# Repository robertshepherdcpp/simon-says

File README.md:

# simon-says
my fourth project for fallout

**what is this project**
- test out your memory with this memory game!
- this project tests your sequence memory, in having a sequence that increases in length after everytime you get it right
- see how far you can go! how many can you remember in a row

**assembly instructions**
- print out the pcb and the case, and purchase the components meantioned in the bom
- put the pcb in the case
- put on the lid. then attach the screws mentioned in the BOM to fix the pcb in place.
- flash the firmware to the xiao-esp32 through the arduino ide (via usb)
- keep it plugged into your computer, as that will be the power source!
- try and see how many you can remember!

**inspiration for the project**
- having played the sequence memory game on [human benchark](humanbenchmark.com), i wanted to have a physical version of this that i could play with!
- i thought it would be a good way to try and improve my memory as having it in physical form i think makes me more likely to use it.

**how it works**
- the project will show the seqence of keys 1 by 1, you simply copy these!
- see how many of these you can remember!
- if you have a high score, the project  will flash 3 times (this high score is stored on the permanent storage of esp-32 board. (using preferences.h)
- if you press the wrong key, then all leds will flash once, and the sequence will reset, (back to a seqeunce of length 1, then you have to memorize a new sequence)
- keep trying to beat the PB!

**how this project was made**
- case made using fusion360
- pcb made using kicad
- in the 3d model, the keycaps and cherry-switches were imported as step files from repos on github.

**screenshots**
the schematic:

the footprint:

pcb 3d:

the 3d model:

zine:

bom:

total project cost: $28.53 (however will already have components spare from other projects like cherry mx switches, key caps)

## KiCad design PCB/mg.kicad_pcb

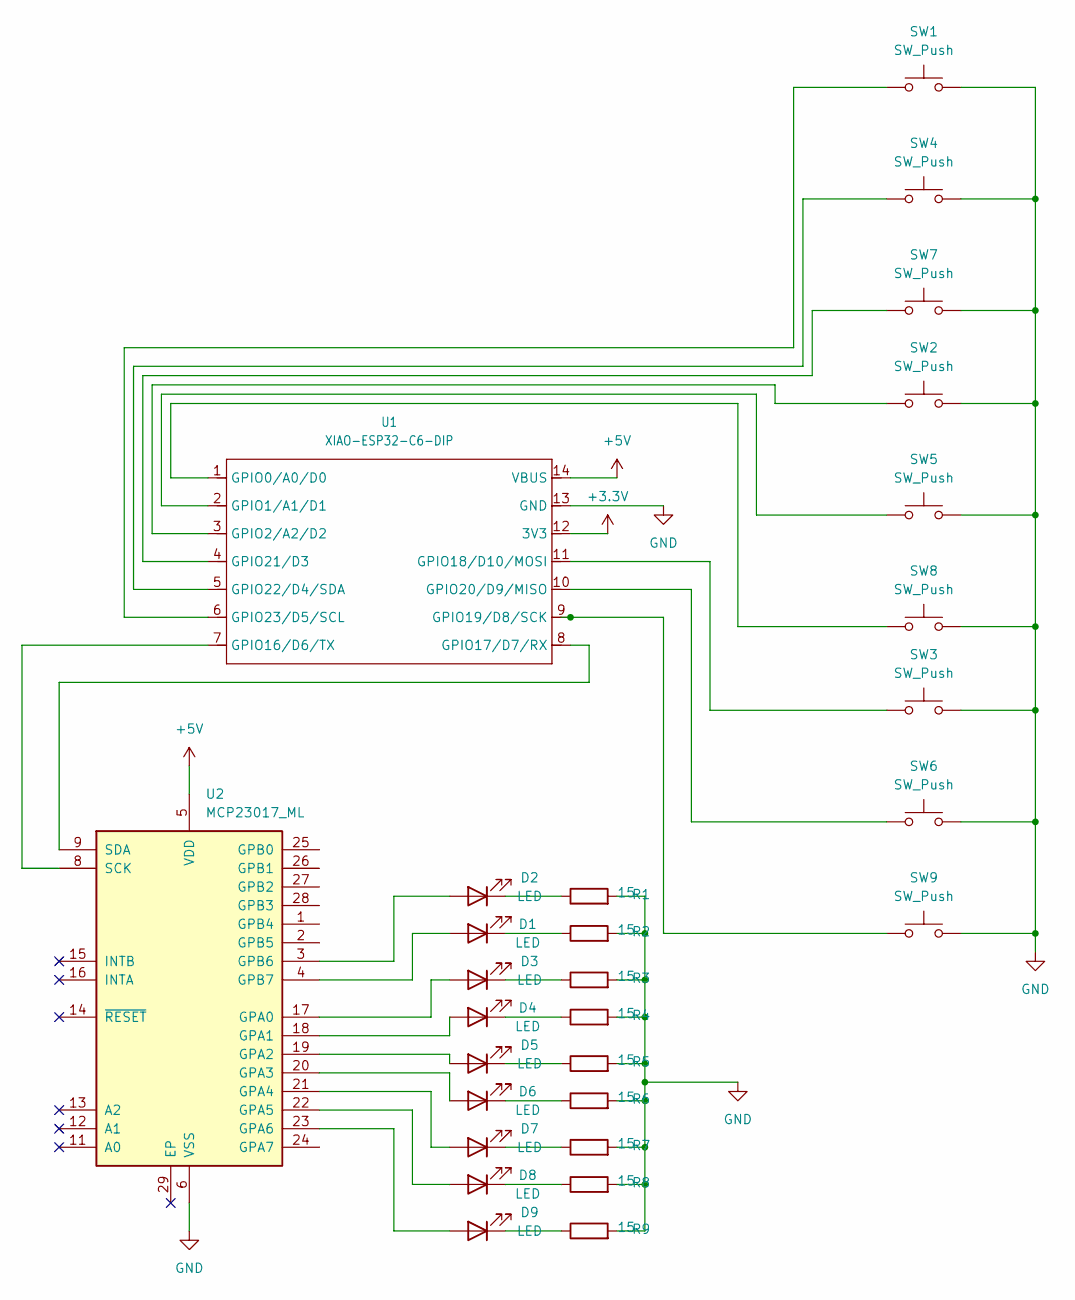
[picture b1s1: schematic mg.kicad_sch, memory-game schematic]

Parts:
D1, D2, D3, D4, D5, D6, D7, D8, D9: LED; LED_0603_1608Metric
R1, R2, R3, R4, R5, R6, R7, R8, R9: 15; R_0603_1608Metric
SW1, SW2, SW3, SW4, SW5, SW6, SW7, SW8, SW9: SW_Push; SW_Cherry_MX_1.00u_PCB
U1: XIAO-ESP32-C6-DIP
U2: MCP23017_ML; QFN-28-1EP_6x6mm_P0.65mm_EP4.25x4.25mm

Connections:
+3.3V: U1.12 (3V3)
+5V: U1.14 (VBUS), U2.5 (VDD)
GND: R1.2, R2.2, R3.2, R4.2, R5.2, R6.2, R7.2, R8.2, R9.2, SW1.2, SW2.2, SW3.2, SW4.2, SW5.2, SW6.2, SW7.2, SW8.2, SW9.2, U1.13 (GND), U2.6 (VSS)
unnamed: D1.2 (A), U2.4 (GPB7)
unnamed: D1.1 (K), R2.1
unnamed: D2.2 (A), U2.3 (GPB6)
unnamed: D2.1 (K), R1.1
unnamed: D3.2 (A), U2.17 (GPA0)
unnamed: D3.1 (K), R3.1
unnamed: D4.2 (A), U2.18 (GPA1)
unnamed: D4.1 (K), R4.1
unnamed: D5.2 (A), U2.19 (GPA2)
unnamed: D5.1 (K), R5.1
unnamed: D6.2 (A), U2.20 (GPA3)
unnamed: D6.1 (K), R6.1
unnamed: D7.2 (A), U2.21 (GPA4)
unnamed: D7.1 (K), R7.1
unnamed: D8.2 (A), U2.22 (GPA5)
unnamed: D8.1 (K), R8.1
unnamed: D9.2 (A), U2.23 (GPA6)
unnamed: D9.1 (K), R9.1
unnamed: SW8.1, U1.1 (GPIO0/A0/D0)
unnamed: SW5.1, U1.2 (GPIO1/A1/D1)
unnamed: SW2.1, U1.3 (GPIO2/A2/D2)
unnamed: U1.7 (GPIO16/D6/TX), U2.8 (SCK)
unnamed: U1.8 (GPIO17/D7/RX), U2.9 (SDA)
unnamed: SW3.1, U1.11 (GPIO18/D10/MOSI)
unnamed: SW9.1, U1.9 (GPIO19/D8/SCK)
unnamed: SW6.1, U1.10 (GPIO20/D9/MISO)
unnamed: SW7.1, U1.4 (GPIO21/D3)
unnamed: SW4.1, U1.5 (GPIO22/D4/SDA)
unnamed: SW1.1, U1.6 (GPIO23/D5/SCL)

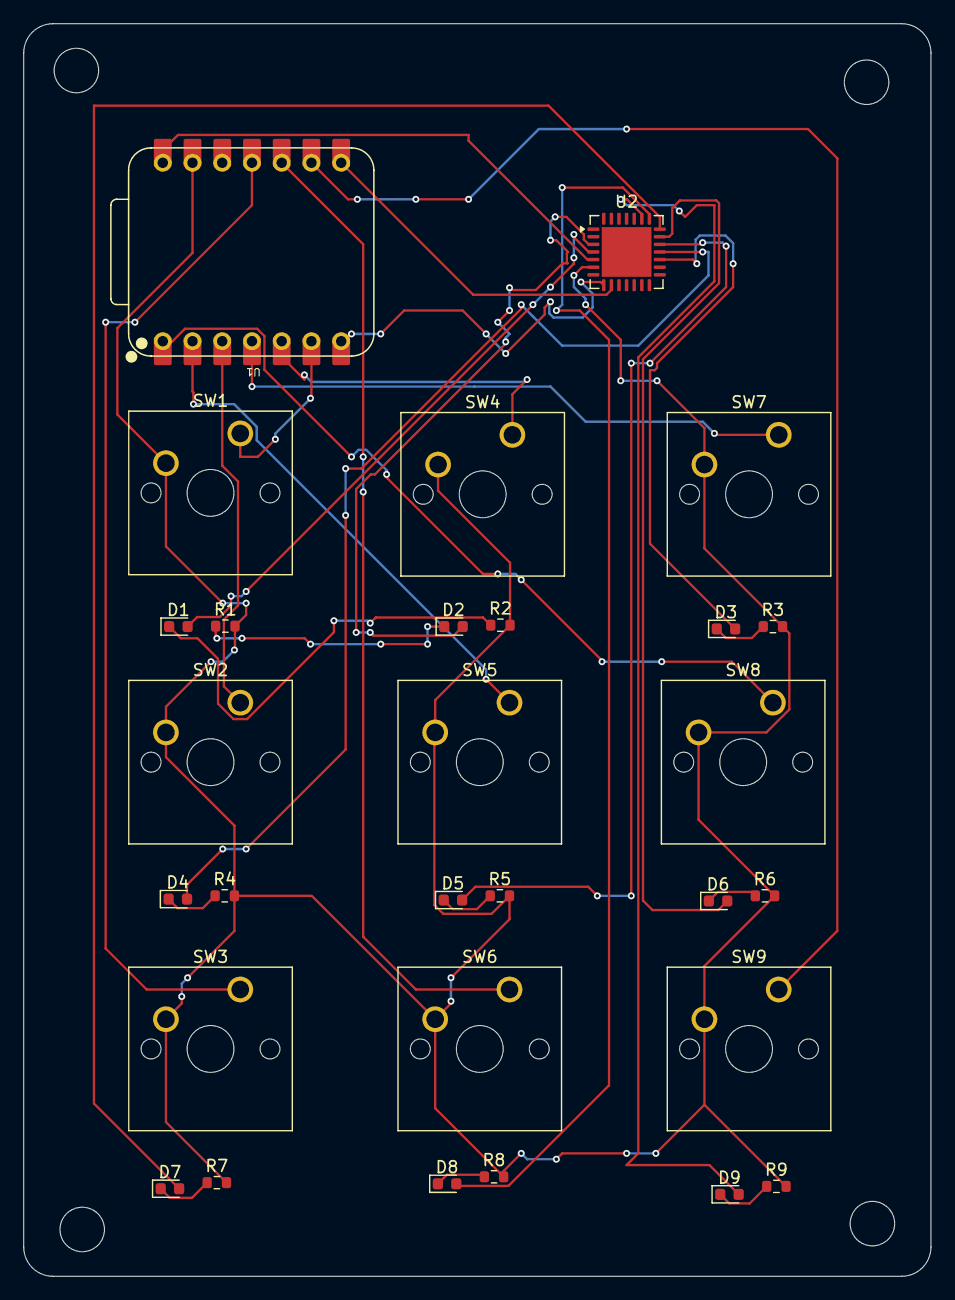
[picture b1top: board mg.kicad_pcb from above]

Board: 2 copper layers, 77.5 x 107.0 mm, 29 parts (0 on the bottom side), 31 nets.

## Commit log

2026-04-29 Enhance README with project information and instructions
    Expanded the README to include project details, usage instructions, inspiration, and how it works.
2026-04-29 add the pcb files
2026-04-29 Rename switch.step to CAD/switch.step
2026-04-29 Rename roductivv.f3d to CAD/roductivv.f3d
2026-04-29 Rename Cherry MX keycaps.step to CAD/Cherry MX keycaps.step
2026-04-29 Rename sketch_apr26a_copy_20260429135617.ino to firmware/sketch_apr26a_copy_20260429135617.ino
2026-04-29 Add new image to README.md zine section
2026-04-29 Rename Untitled (1).png to Zine/zine.png
2026-04-29 Update total project cost from $26.73 to $36.28
    Updated total project cost in the README.
2026-04-29 Fix formatting issue in BOM CSV for MCP23017
2026-04-29 Add BOM image and project cost information
    Added an image for the BOM section and provided cost details.
2026-05-01 Update README with additional information on usage
    Added a note about the 'how it works' section for more information.
2026-06-04 add the actual mcp23017 chip
2026-06-04 add new zine
2026-06-04 Rename Untitled (13).pdf to zine.pdf
2026-06-04 Update README with additional zine image
    Added a new image to the zine section of the README.
2026-06-04 add the updataed cherry mx keycaps step file
2026-06-09 Add total cost row to BOM CSV
2026-06-09 uploading the new pcb files (with the cutout in the pcb)
2026-06-09 Update images in README.md
    Removed and replaced images in the README.
2026-06-09 add the new zine.
2026-06-09 Rename Untitled (18).pdf to zine.pdf
2026-06-09 add the updated gerber files.
2026-06-09 add the cad files.
2026-06-11 added the updated zine.
2026-06-12 Replace image in zine section of README
2026-06-15 Revise assembly instructions in README
    Updated assembly instructions for clarity and detail.
2026-06-15 Replace old image with a new one in README
2026-06-15 add the updated zine (a few little moving of assets and making the squares a bit more round)
2026-06-15 add new zine.
2026-06-20 Change product links to AliExpress
    Updated product links to point to AliExpress for better availability.
2026-06-20 add updated schematic.
2026-06-20 add updated schematic image to the readme.
2026-06-20 Replace image in README with updated version
2026-06-20 add updated pcb files.
2026-06-20 Rename Untitled (26).pdf to zine.pdf
2026-06-20 add updated zine image.
